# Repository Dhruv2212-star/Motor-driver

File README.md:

The schematic is divided into 2 parts for easier designing-  
1. Power distribution system
2. Logic system

1. **Block 1 – Power System**
Objective-  

The Power System is responsible for receiving power from the battery, protecting the circuit from electrical faults, filtering supply noise, and delivering a clean, protected power rail to the motor driver IC. Every component in this block contributes to either protection, power conditioning, or power distribution.  
| Ref    | Component               | Selected Part                   | Why this part was used and what role it plays                                                                                                                                                                                                                                                                                                                                         |
| ------ | ----------------------- | ------------------------------- | ------------------------------------------------------------------------------------------------------------------------------------------------------------------------------------------------------------------------------------------------------------------------------------------------------------------------------------------------------------------------------------- |
| **J1** | Power Input Connector   | Phoenix Contact MKDS 1,5/2-5.08 | J1 serves as the entry point for the external power supply. A screw terminal was selected because it provides a secure, reliable, and vibration-resistant connection for battery wires while allowing easy installation and removal during testing or maintenance.                                                                                                                    |
| **F1** | Resettable Polyfuse     | Bourns MF-R250                  | The MF-R250 was chosen to protect the entire PCB from excessive current caused by short circuits or wiring faults. Unlike a traditional fuse, it automatically resets after the fault is removed, eliminating the need for replacement. It is placed immediately after the power connector so every downstream component is protected.                                                |
| **Q1** | P-Channel MOSFET        | AO3407A                         | The AO3407A was selected to provide reverse-polarity protection with almost no voltage drop. If the battery is connected correctly, the MOSFET conducts normally with very low resistance. If the battery is connected in reverse, it blocks current completely, preventing damage to the rest of the circuit. This method is significantly more efficient than using a series diode. |
| **R1** | Gate Pull-Down Resistor | 100 kΩ                          | The 100 kΩ resistor ensures that the MOSFET gate is always held at a defined voltage during power-up and power-down. This guarantees predictable switching behavior and prevents the MOSFET from turning on unintentionally due to electrical noise or a floating gate.                                                                                                               |
| **D1** | TVS Diode               | SMBJ15A                         | The SMBJ15A TVS diode was selected to protect the circuit from sudden voltage spikes and transients generated by motors, wiring inductance, or external power disturbances. Under normal operating conditions it remains inactive, but during an over-voltage event it quickly clamps the voltage to a safe level, protecting sensitive components.                                   |
| **C1** | Bulk Capacitor          | 470 µF, 25 V Electrolytic       | C1 acts as the primary energy reservoir for the motor supply. Motors can draw large bursts of current during startup or rapid direction changes, causing the supply voltage to dip. This capacitor supplies that short-term current, reducing voltage fluctuations and improving overall system stability.                                                                            |
| **C2** | Decoupling Capacitor    | 100 nF Ceramic                  | While C1 handles low-frequency voltage fluctuations, C2 removes high-frequency electrical noise generated by switching circuits and motor commutation. Ceramic capacitors have very low impedance at high frequencies, making them ideal for filtering fast voltage spikes that electrolytic capacitors cannot effectively suppress.                                                  |

2. **Block 2 – Motor Driver System**
Objective-  

The Motor Driver System receives logic commands from an external microcontroller and controls two DC motors using the TB6612FNG dual H-bridge driver. It also provides the required power conditioning for the IC and exposes the motor outputs through dedicated connectors.

| Ref    | Component                         | Selected Part                   | Why this part was used and what role it plays                                                                                                                                                                                                                                                                            |
| ------ | --------------------------------- | ------------------------------- | ------------------------------------------------------------------------------------------------------------------------------------------------------------------------------------------------------------------------------------------------------------------------------------------------------------------------ |
| **U1** | Dual H-Bridge Motor Driver        | TB6612FNG                       | The TB6612FNG was selected because it is a reliable dual H-bridge motor driver capable of independently controlling two DC motors. It supports PWM speed control, forward/reverse operation, braking, and standby mode while offering significantly lower power loss than older bipolar motor drivers such as the L298N. |
| **J2** | Logic Interface Header            | 1×9 Pin Header                  | J2 provides the electrical interface between the motor driver PCB and an external microcontroller such as an STM32, Arduino, or ESP32. It carries all required logic signals including PWM inputs, direction control, standby control, logic power, and ground.                                                          |
| **J3** | Motor A Connector                 | Phoenix Contact MKDS 1,5/2-5.08 | J3 provides a secure connection between the motor driver outputs and Motor A. A screw terminal was selected to allow easy connection and replacement of motors while providing reliable electrical contact under vibration and higher current conditions.                                                                |
| **J4** | Motor B Connector                 | Phoenix Contact MKDS 1,5/2-5.08 | J4 performs the same function as J3 for Motor B, providing a durable and removable connection for the second motor output.                                                                                                                                                                                               |
| **C3** | Logic Supply Decoupling Capacitor | 100 nF Ceramic                  | C3 stabilizes the logic supply (VCC) of the TB6612FNG by filtering high-frequency noise. This prevents disturbances from affecting the IC's internal control circuitry and improves overall reliability.                                                                                                                 |
| **C4** | Motor Supply Decoupling Capacitor | 100 nF Ceramic                  | C4 filters high-frequency switching noise present on the motor supply (VM). It is positioned close to the motor driver IC to minimize voltage spikes caused by the rapid switching of the internal MOSFETs.                                                                                                              |
| **C5** | Bulk Motor Supply Capacitor       | 10 µF, 25 V Electrolytic        | C5 provides additional local energy storage directly beside the motor driver IC. During sudden motor current demands, it supplies instant current to the TB6612FNG, helping maintain a stable VM supply and reducing voltage dips on the PCB.

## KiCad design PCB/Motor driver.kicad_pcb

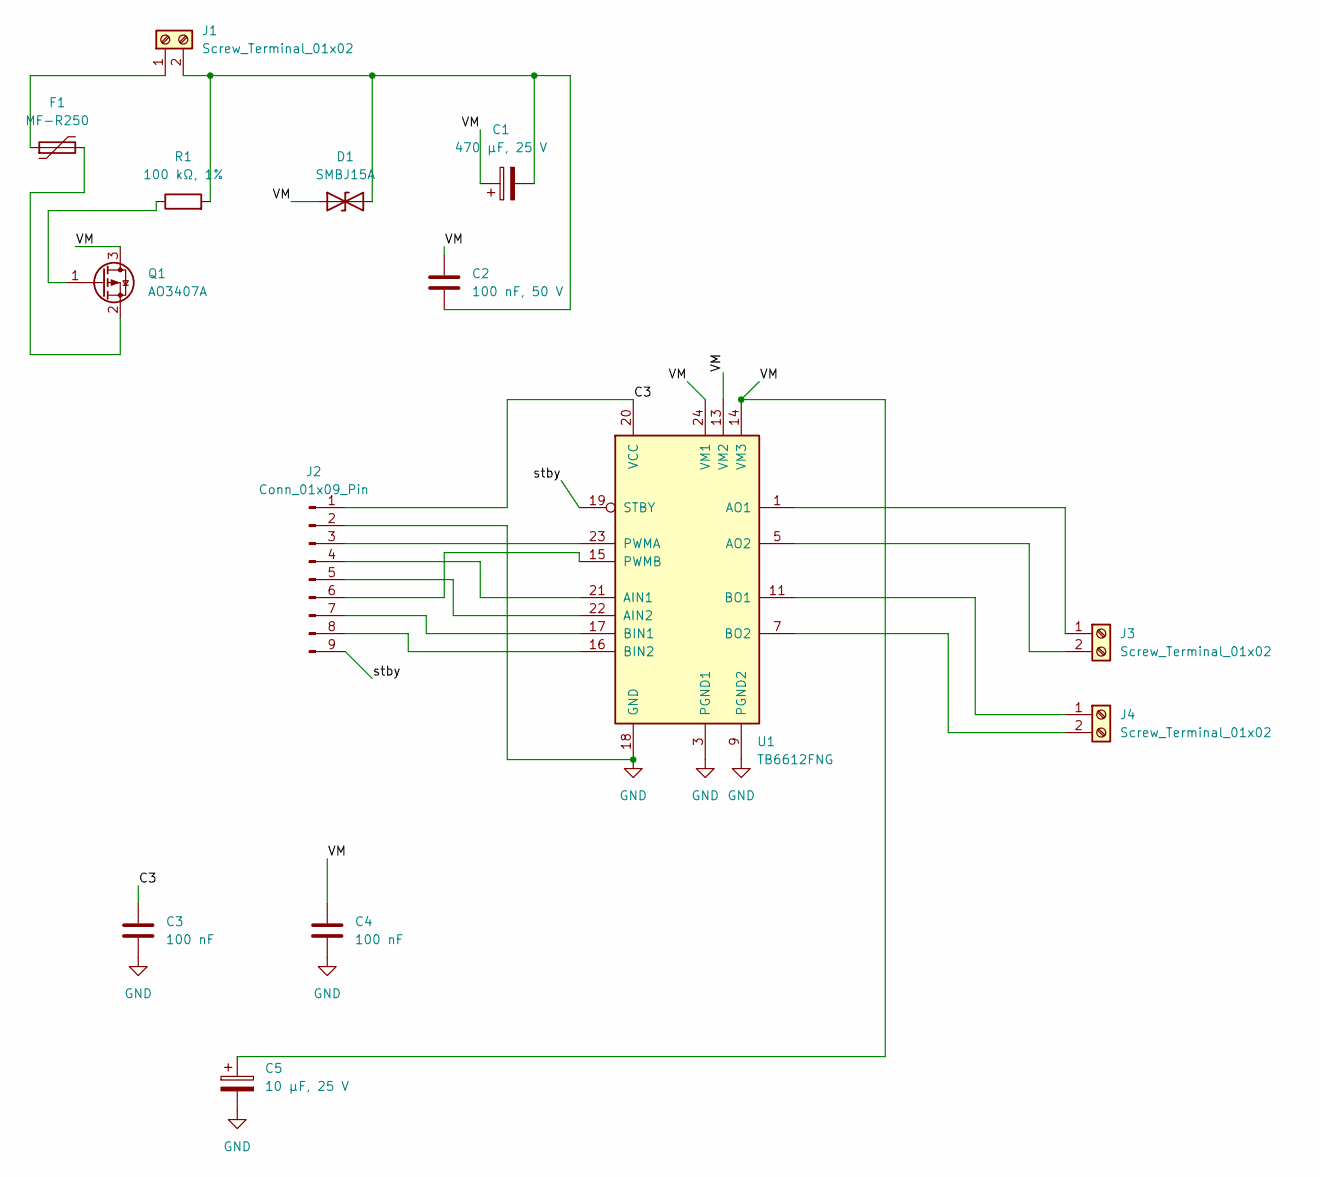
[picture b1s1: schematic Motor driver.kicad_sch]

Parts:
C1: 470 µF, 25 V; CP_Radial_D10.0mm_P5.00mm
C2: 100 nF, 50 V; C_0805_2012Metric
C3, C4: 100 nF; C_0805_2012Metric
C5: 10 µF, 25 V; CP_Radial_D5.0mm_P2.00mm
D1: SMBJ15A; D_SMB
F1: MF-R250; Fuse_Bourns_MF-RG300
J1, J3, J4: Screw_Terminal_01x02; TerminalBlock_Phoenix_MKDS-1,5-2-5.08_1x02_P5.08mm_Horizont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
J2: Conn_01x09_Pin; PinHeader_1x09_P2.54mm_Vertical
Q1: AO3407A; SOT-23
R1: 100 kΩ, 1%; R_0805_2012Metric
U1: TB6612FNG; SSOP-24_5.3x8.2mm_P0.65mm

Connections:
/C3: C3.1, J2.1, U1.20 (VCC)
/VM: C1.1, C2.1, C4.1, C5.1, D1.1 (A1), Q1.3 (D), U1.13 (VM2), U1.14 (VM3), U1.24 (VM1)
/stby: J2.9, U1.19 (STBY)
GND: C3.2, C4.2, C5.2, J2.2, U1.3 (PGND1), U1.4 (PGND1), U1.9 (PGND2), U1.10 (PGND2), U1.18 (GND)
unnamed: C1.2, C2.2, D1.2 (A2), J1.2, R1.2
unnamed: F1.1, J1.1
unnamed: J2.3, U1.23 (PWMA)
unnamed: J2.4, U1.21 (AIN1)
unnamed: J2.5, U1.22 (AIN2)
unnamed: J2.6, U1.15 (PWMB)
unnamed: J2.7, U1.17 (BIN1)
unnamed: J2.8, U1.16 (BIN2)
unnamed: J3.1, U1.1 (AO1), U1.2 (AO1)
unnamed: J3.2, U1.5 (AO2), U1.6 (AO2)
unnamed: J4.1, U1.11 (BO1), U1.12 (BO1)
unnamed: J4.2, U1.7 (BO2), U1.8 (BO2)
unnamed: Q1.1 (G), R1.1
unnamed: F1.2, Q1.2 (S)

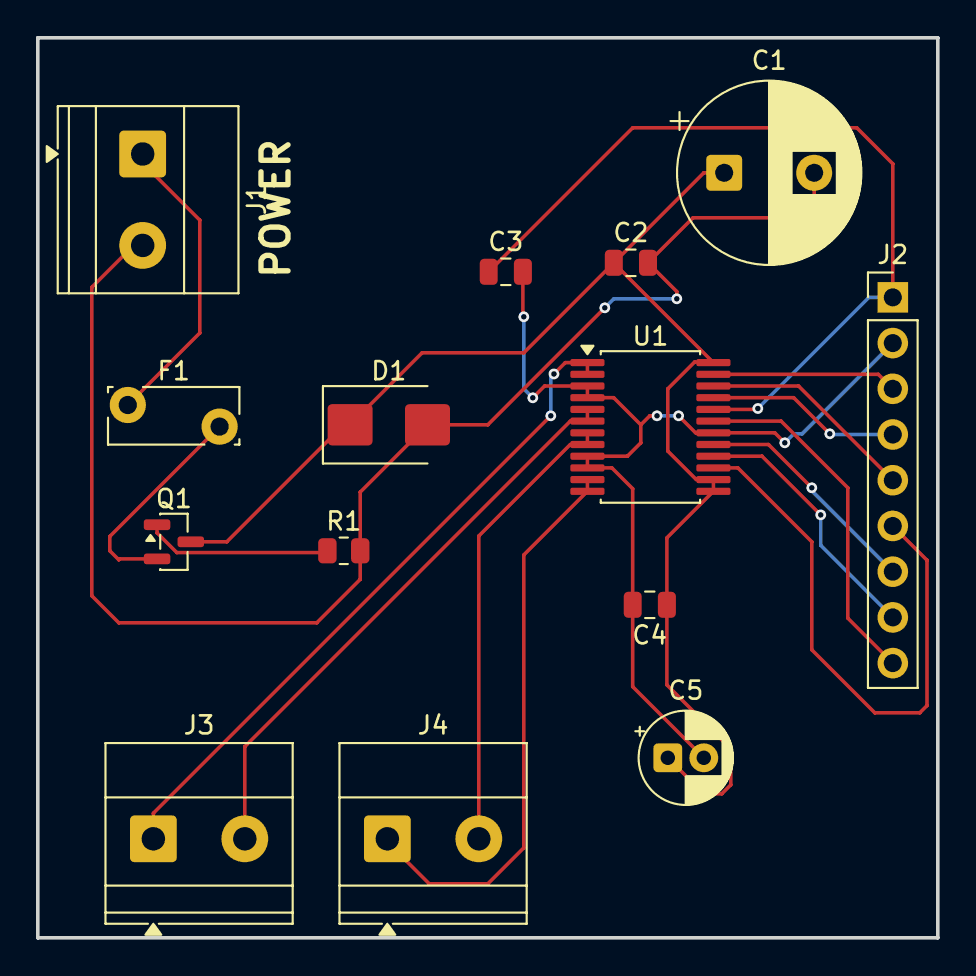
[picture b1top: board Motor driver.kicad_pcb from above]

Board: 2 copper layers, 50.0 x 50.0 mm, 14 parts (0 on the bottom side), 18 nets.
